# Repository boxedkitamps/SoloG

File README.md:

<b>Boxed Kit Amps SoloG</b><p>
Pocket Guitar Amp<p>
licensed under Creative Commons CC BY-SA-NC 2.5<br>
Contact: <em>http://www.boxedkitamps.com</em><br>
Open Source: <em>https://github.com/boxedkitamps/SoloG</em>

soloG.brd - Eagle layout

soloG.sch - Eagle schematic

<<<<<<< HEAD
SoloG-fpX1.svg - Face Plate

=======
soloG.scr, soloG.lbr - Eagle exports

SoloG-fpX1.svg - Face Plate
>>>>>>> 9476066ee1e3237a81e3fb47cee19a7d675c86cc

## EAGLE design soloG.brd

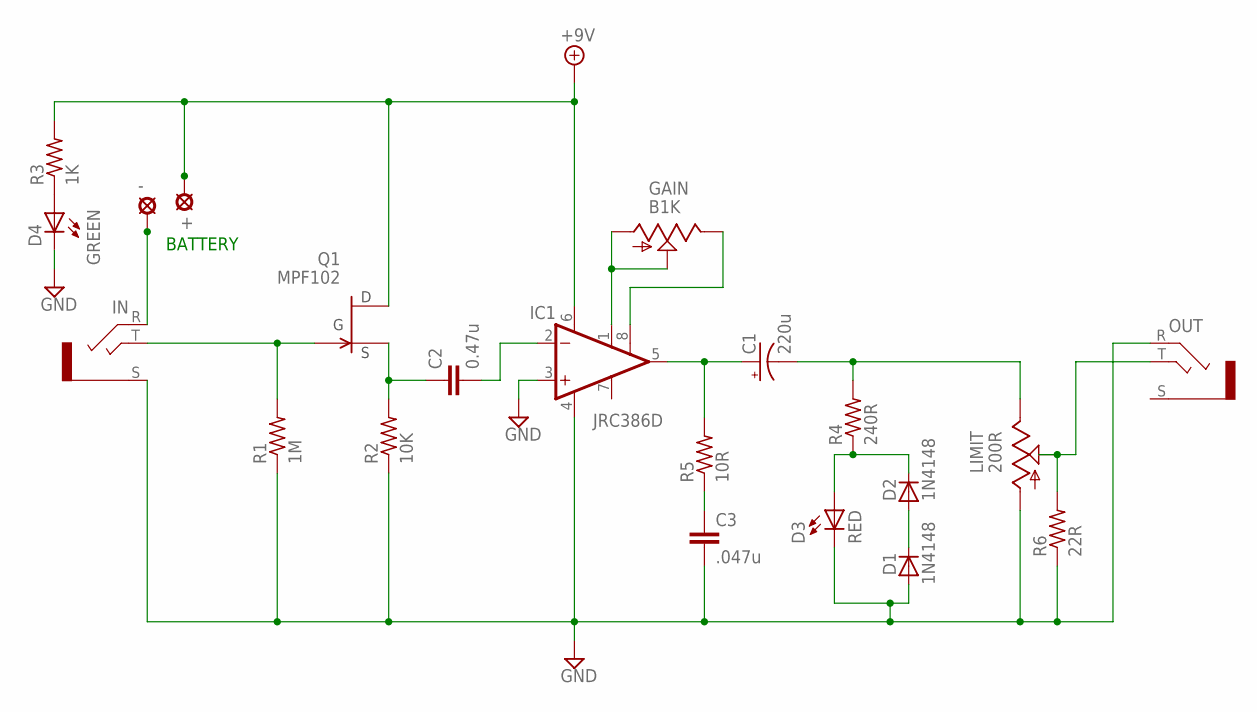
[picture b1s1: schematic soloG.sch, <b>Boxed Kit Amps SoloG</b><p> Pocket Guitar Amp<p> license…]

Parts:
+: SOLPAD
-: SOLPAD
C1: 220u; E3,5-8
C2: 0.47u; C15B5
C3: .047u; C075-040X085_OVAL
D1, D2: 1N4148; DO35-7
D3: RED; LED3MM
D4: GREEN; LED3MM
GAIN: B1K; PTD901-2015K
IC1: JRC386D; DIP8
IN: NRJ6-STEREO-HH; NRJ6HH
LIMIT: 200R; 0655-614
OUT: NRJ6-STEREO-HH; NRJ6HH
Q1: MPF102; TO92-FET
R1: 1M; 0207/7
R2: 10K; 0207/7
R3: 1K; 0207/7
R4: 240R; 0207/7
R5: 10R; 0207/7
R6: 22R; 0207/7

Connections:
+9V: +.1, IC1.6 (VS), Q1.D, R3.2
GND: C3.P$2 (2), D1.A, D3.K (C), D4.K (C), IC1.3 (+IN), IC1.4 (GND), IN.S (3), LIMIT.A, OUT.R (2), R1.1, R2.1, R6.1
unnamed: C1.+, IC1.5 (OUT), R5.2
unnamed: C2.1, Q1.S, R2.2
unnamed: GAIN.1 (A), GAIN.2 (S), IC1.1 (GAIN)
unnamed: C2.2, IC1.2 (-IN)
unnamed: -.1, IN.R (2)
unnamed: IN.T (1), Q1.G, R1.2
unnamed: C3.P$1 (1), R5.1
unnamed: LIMIT.S, OUT.T (1), R6.2
unnamed: GAIN.3 (E), IC1.8 (GAIN)
unnamed: D4.A, R3.1
unnamed: D2.C, D3.A, R4.1
unnamed: C1.-, LIMIT.E, R4.2
unnamed: D1.C, D2.A

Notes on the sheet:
BATTERY

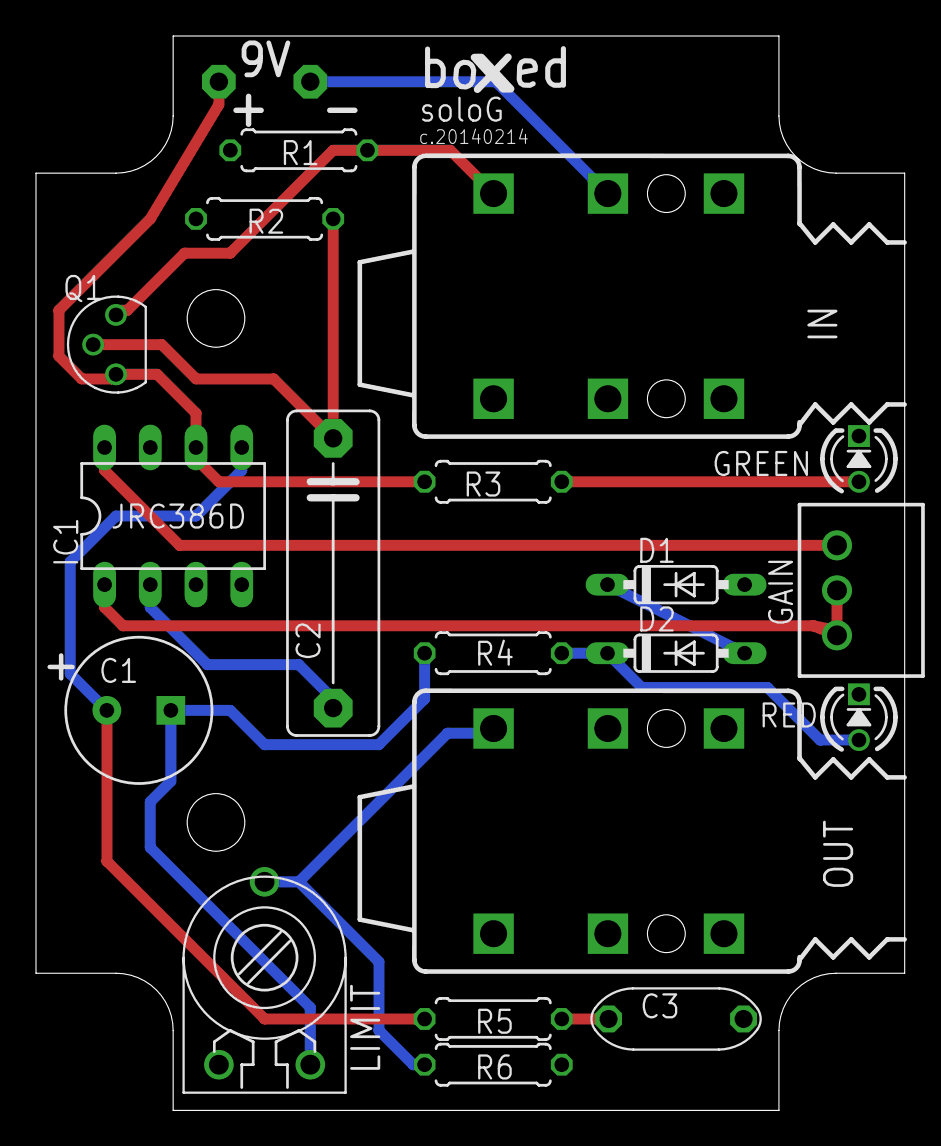
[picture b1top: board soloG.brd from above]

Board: 2 copper layers, 48.3 x 59.7 mm, 21 parts (0 on the bottom side), 15 nets.

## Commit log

2014-05-10 Eagle files
2014-05-10 face plate
2014-05-10 Eagle libraries, face plate
2014-05-10 license
2014-05-10 licensed
2014-05-10 description
